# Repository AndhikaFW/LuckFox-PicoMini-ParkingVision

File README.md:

# LuckFox-PicoMini-ParkingVision

A distributed smart parking monitoring vision system utilizing **LuckFox Pico Mini** AI camera boards paired with **ESP32-S3 RAP** nodes, chained together and bridged to a Raspberry Pi 4 backend over wired Ethernet.

Every node in this project is a **parking lot** -- there is no separate entrance/gate node yet (may be added later as its own thing).

---

## System Components (per node)

Each parking-lot node is one **LuckFox Pico Mini** + one **ESP32-S3**, wired together over SPI:

1. **LuckFox Pico Mini (RV1103) -- on-device vision AI**
   - Reads a camera feed, encodes/splits it into **3x 600x400 video streams**.
   - Pipeline per stream: motion detection -> AI car detection -> sleep briefly -> occupancy check (vacant/occupied) -> if occupied, crop + OCR the plate.
   - Sends the 3 encoded video streams and, if present, the cropped plate result to its paired ESP32-S3.

2. **ESP32-S3 RAP (chain relay + one Gateway uplink)**
   - Runs the exact same firmware on every unit (see [`src/ESP32-S3-RAP`](src/ESP32-S3-RAP)); role and chain position come from a small per-unit provisioning step, not a separate build.
   - One designated node (`node_id == 0`, the **Gateway**) also carries a **W5500** module and bridges to the Raspberry Pi 4 backend over a direct Ethernet cable (RJ45) -- it's still a parking-lot node like any other, just the one with this extra uplink role.

---

## Network Architecture: Chain (not a closed ring)

Despite the "RAP" (Ring Access Protocol) name -- kept from this project's original design for naming continuity (`ring_size`, `node_id`, etc. still appear throughout) -- the topology is a **one-way chain**, not a closed loop: there's no "first" node and the Gateway has no outgoing link back into the chain, it only sinks data out to the RPi4.

Every node has its own initiative: it originates its own occupancy/plate reading and video frames on its own schedule, and relays whatever it receives from its upstream neighbor (`prev`) toward its downstream neighbor (`next`) -- both interleaved through the same per-hop link. Two independent transports run in parallel over the same radio:

- **ESP-NOW** -- small `StatusPacket`s (`origin_node_id`, `seq`, `occupied`, `plate`), hop-by-hop with stop-and-wait flow control (a node only accepts a new packet from `prev` once it has room to forward it to `next`).
- **WiFi AP+STA daisy-chain (TCP)** -- bulk video, since raw frames are far too large for ESP-NOW's 250-byte limit. Each frame carries `{origin_node_id, stream_id, seq, data_len}` so its source lot and camera are always identifiable, even after several relay hops.

```mermaid
graph LR
    subgraph "Chain Network (one-way, no closing loop)"
        Node1["Lot 1<br>(LuckFox + ESP32-S3)"] -->|"status/plate + video"| Node2["Lot 2<br>(LuckFox + ESP32-S3)"]
        Node2 -->|"status/plate + video"| Node3["Lot 3<br>(LuckFox + ESP32-S3)"]
        Node3 -->|"status/plate + video"| NodeN["... Lot N-1"]
        NodeN -->|"status/plate + video"| Gateway["Lot 0 / GATEWAY<br>(LuckFox + ESP32-S3 + W5500)"]
    end

    Gateway -->|"RJ45 (W5500), status:5000 video:5300"| RPi["Raspberry Pi 4 backend"]
```

### Why a chain instead of a mesh/star

- **Deterministic, low-collision flow**: every hop is a simple point-to-point link (ESP-NOW unicast + a WiFi AP/STA pair), so there's no contention/arbitration between nodes for a shared medium.
- **Backpressure, not packet loss**: per-hop stop-and-wait means a slow/busy hop naturally throttles the whole chain instead of dropping data silently.
- **Simple cabling-free daisy-chaining**: adding a lot just means provisioning one more node with the next `node_id`; no rewiring of a shared bus or router needed.

Self-healing/re-routing around a permanently dead node is **not** implemented yet -- see `docs/network/topology.md` in the submodule for the full list of current limitations.

---

## Data reaching the backend

Both channels tag every reading/frame with `origin_node_id`, so the Raspberry Pi 4 backend can always tell which lot (and, for video, which of its 3 cameras) a piece of data came from:

| Channel | Port | Content |
| :--- | :--- | :--- |
| Status/plate | 5000 | One line per reading: `node_id:occupied:plate` |
| Video | 5300 | Binary, one frame per message: `{origin_node_id, stream_id, seq, data_len}` + raw frame bytes |

Naming a lot (e.g. "Lot A0") is a Raspberry Pi-side concern, not firmware: see [`backend/node_names.json`](backend/node_names.json) and the demo listener scripts in the same folder (`status_listener.py`, `video_listener.py`), which resolve `node_id -> name` and prove data is separable/displayable per lot. This `backend/` folder is plain Python living directly in this repo (not the ESP32 firmware submodule, and not a submodule itself) -- it's Raspberry Pi-side code, kept separate from the ESP32-S3 firmware.

---

## Getting Started

### Cloning the Repository
```bash
git clone --recurse-submodules https://github.com/AndhikaFW/LuckFox-PicoMini-ParkingVision.git
```

If already cloned without submodules:
```bash
git submodule update --init --recursive
```

### Layout

- [`src/ESP32-S3-RAP`](src/ESP32-S3-RAP) -- ESP32-S3 firmware **only** (its own git submodule/repo). Build/flash/provisioning instructions and the full protocol/topology write-up live there: [`docs/network/topology.md`](src/ESP32-S3-RAP/docs/network/topology.md).
- [`backend/`](backend) -- Raspberry Pi 4-side Python (demo listeners + `node_names.json`). Plain files in this repo, not inside the firmware submodule and not a submodule of its own -- there's nothing here that needs its own version history separate from the rest of this repo.

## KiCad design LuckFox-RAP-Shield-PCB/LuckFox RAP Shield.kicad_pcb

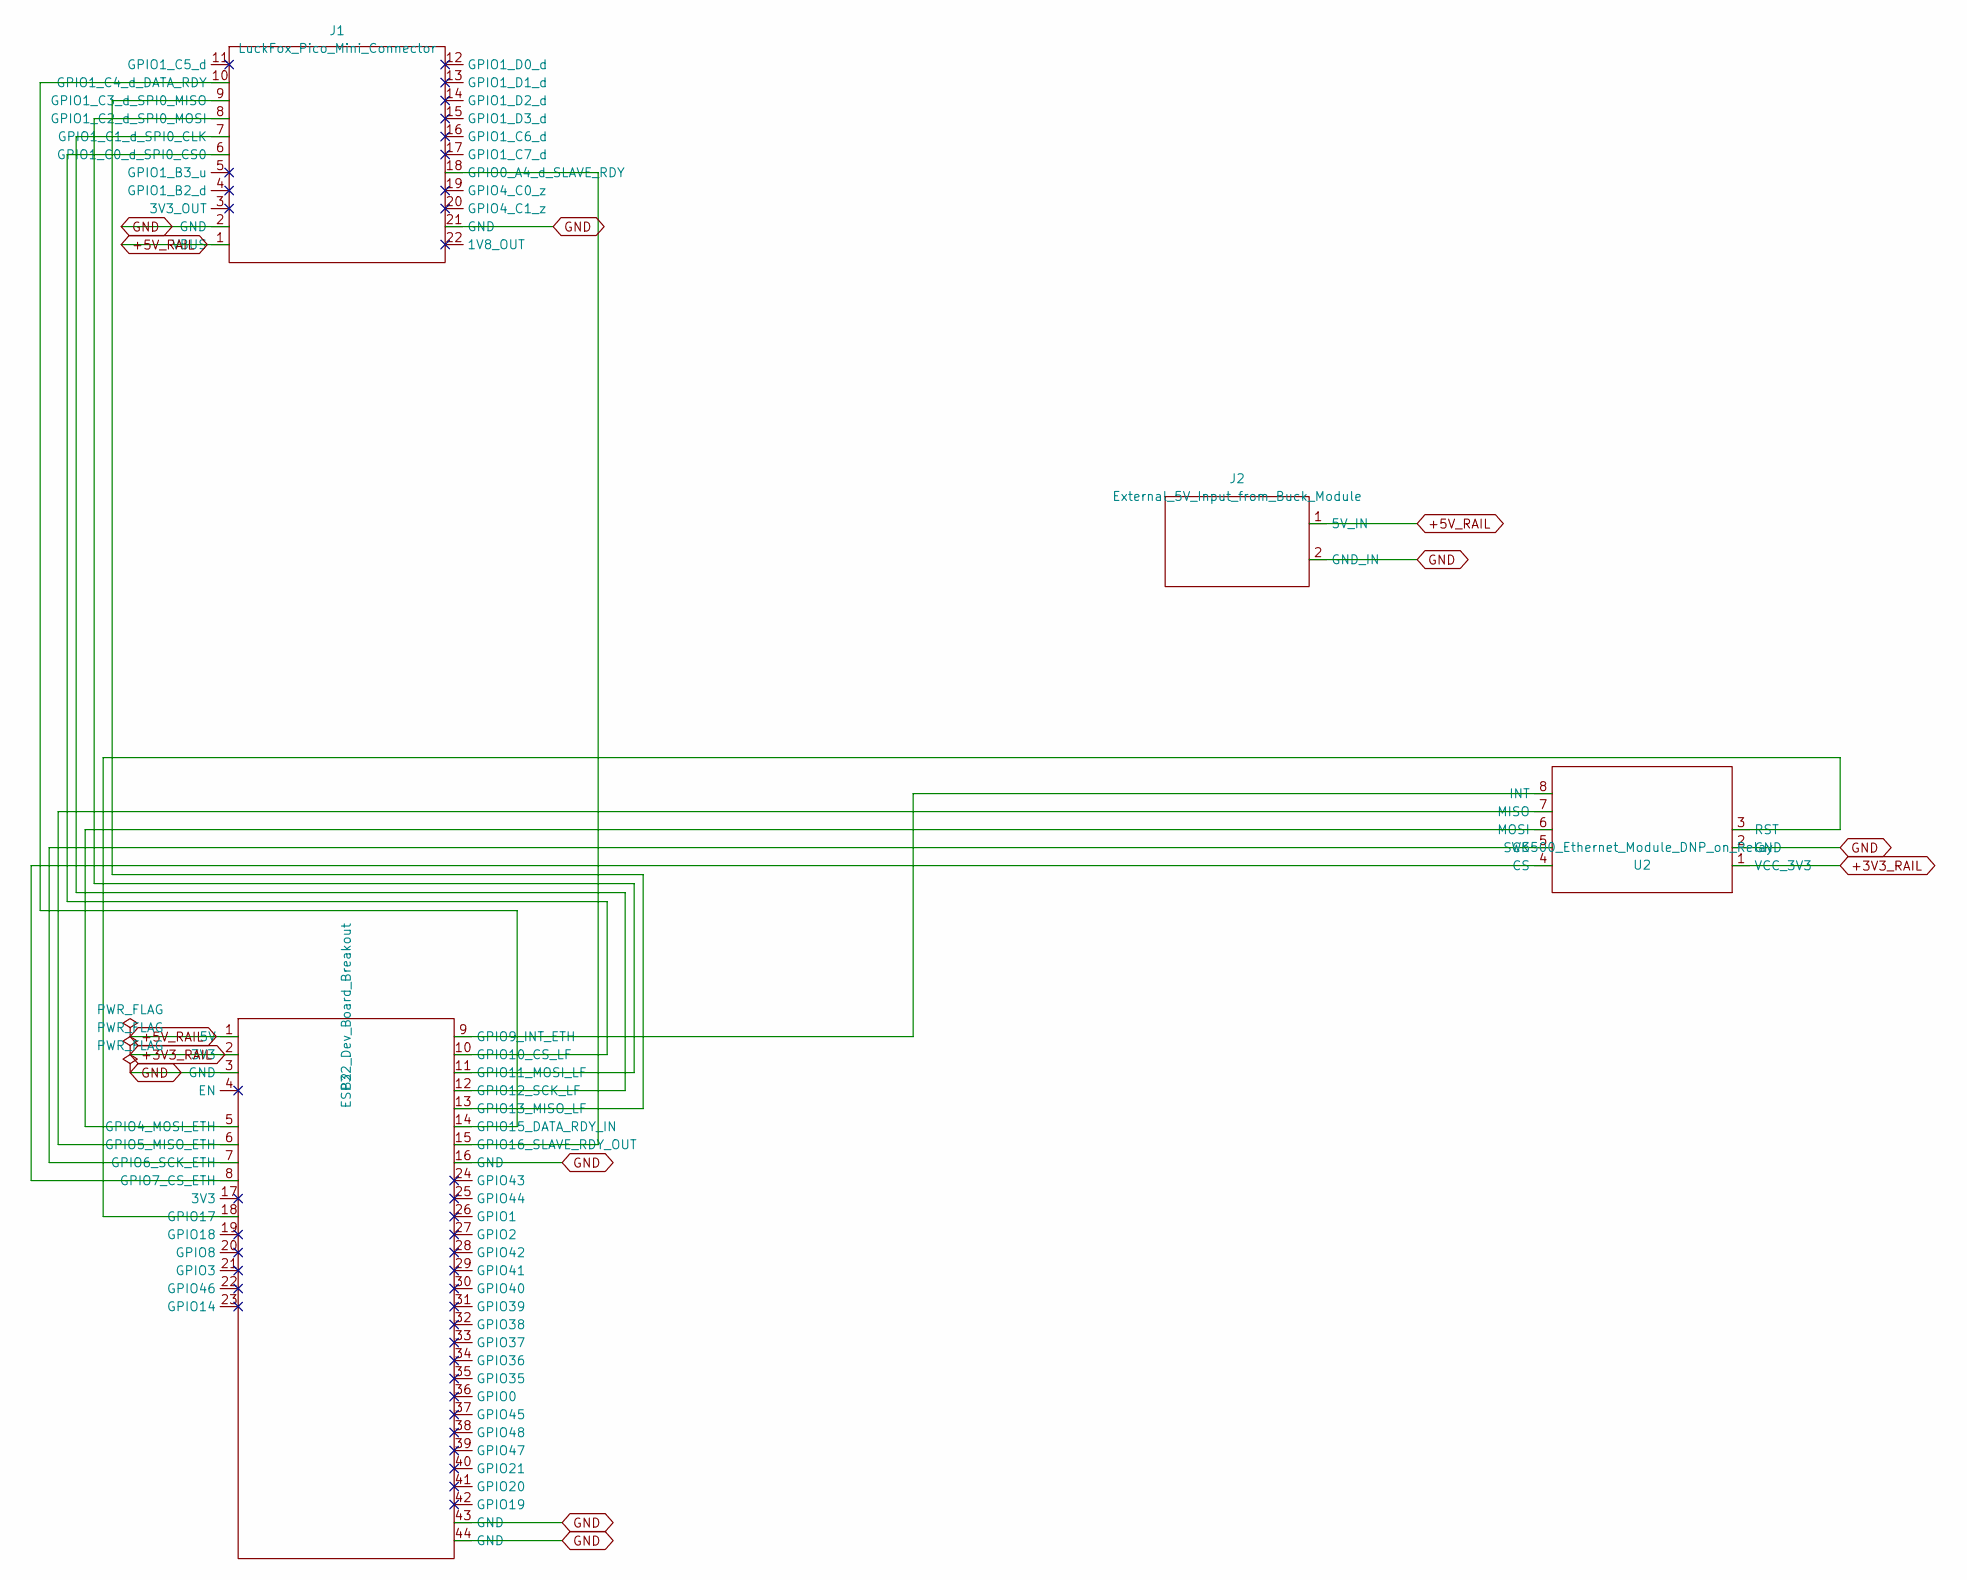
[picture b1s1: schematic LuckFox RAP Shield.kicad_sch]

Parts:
B2: ESP32_Dev_Board_Breakout
J1: LuckFox_Pico_Mini_Connector; LuckFox_Pico_Mini
J2: External_5V_Input_from_Buck_Module; PinHeader_1x02_P2.54mm_Vertical
U2: W5500_Ethernet_Module_DNP_on_Relay; PinHeader_1x08_P2.54mm_Vertical

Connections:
+3V3_RAIL: B2.2 (3V3), U2.1 (VCC_3V3)
+5V_RAIL: B2.1 (5V), J1.1 (VBUS), J2.1 (5V_IN)
GND: B2.3 (GND), B2.16 (GND), B2.43 (GND), B2.44 (GND), J1.2 (GND), J1.21 (GND), J2.2 (GND_IN), U2.2 (GND)
unnamed: B2.5 (GPIO4_MOSI_ETH), U2.6 (MOSI)
unnamed: B2.6 (GPIO5_MISO_ETH), U2.7 (MISO)
unnamed: B2.7 (GPIO6_SCK_ETH), U2.5 (SCK)
unnamed: B2.8 (GPIO7_CS_ETH), U2.4 (CS)
unnamed: B2.9 (GPIO9_INT_ETH), U2.8 (INT)
unnamed: B2.10 (GPIO10_CS_LF), J1.6 (GPIO1_C0_d_SPI0_CS0)
unnamed: B2.11 (GPIO11_MOSI_LF), J1.8 (GPIO1_C2_d_SPI0_MOSI)
unnamed: B2.12 (GPIO12_SCK_LF), J1.7 (GPIO1_C1_d_SPI0_CLK)
unnamed: B2.13 (GPIO13_MISO_LF), J1.9 (GPIO1_C3_d_SPI0_MISO)
unnamed: B2.14 (GPIO15_DATA_RDY_IN), J1.10 (GPIO1_C4_d_DATA_RDY)
unnamed: B2.15 (GPIO16_SLAVE_RDY_OUT), J1.18 (GPIO0_A4_d_SLAVE_RDY)
unnamed: B2.18 (GPIO17), U2.3 (RST)

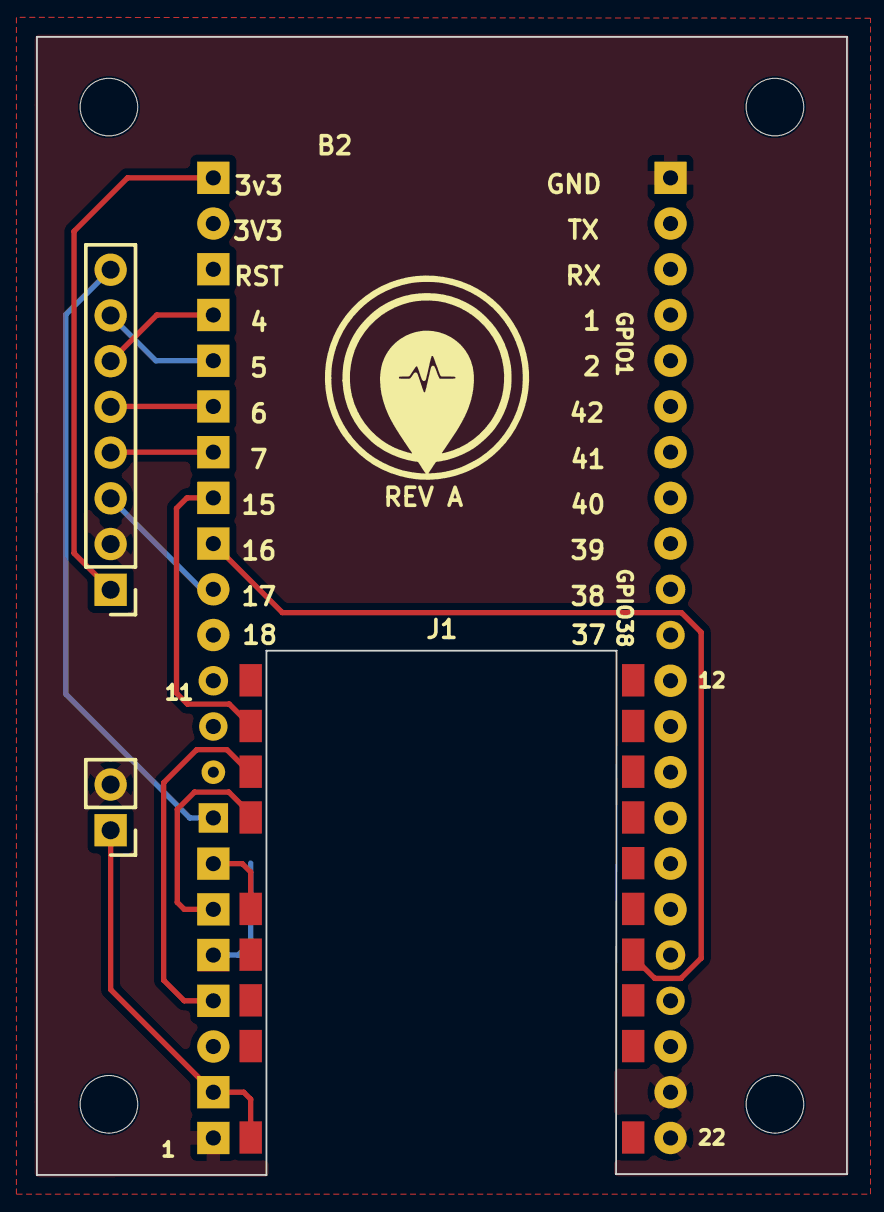
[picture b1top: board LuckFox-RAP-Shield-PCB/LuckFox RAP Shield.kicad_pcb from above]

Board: 2 copper layers, 45.0 x 63.2 mm, 8 parts (1 on the bottom side), 15 nets.

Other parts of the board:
H1, H2, H3, H4: MountingHole_3.2mm_M3

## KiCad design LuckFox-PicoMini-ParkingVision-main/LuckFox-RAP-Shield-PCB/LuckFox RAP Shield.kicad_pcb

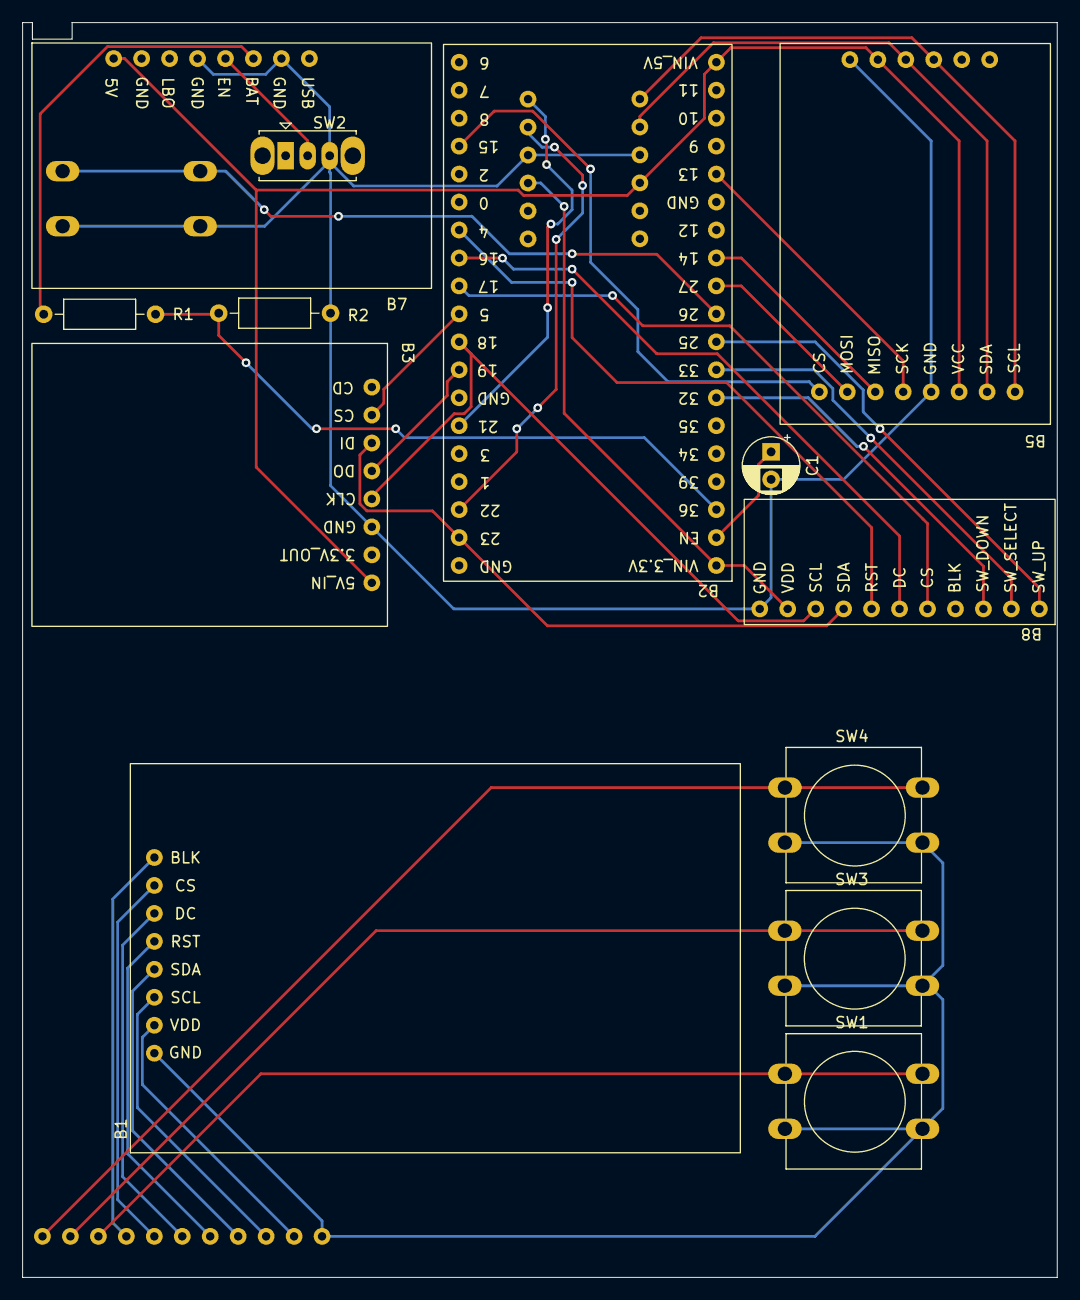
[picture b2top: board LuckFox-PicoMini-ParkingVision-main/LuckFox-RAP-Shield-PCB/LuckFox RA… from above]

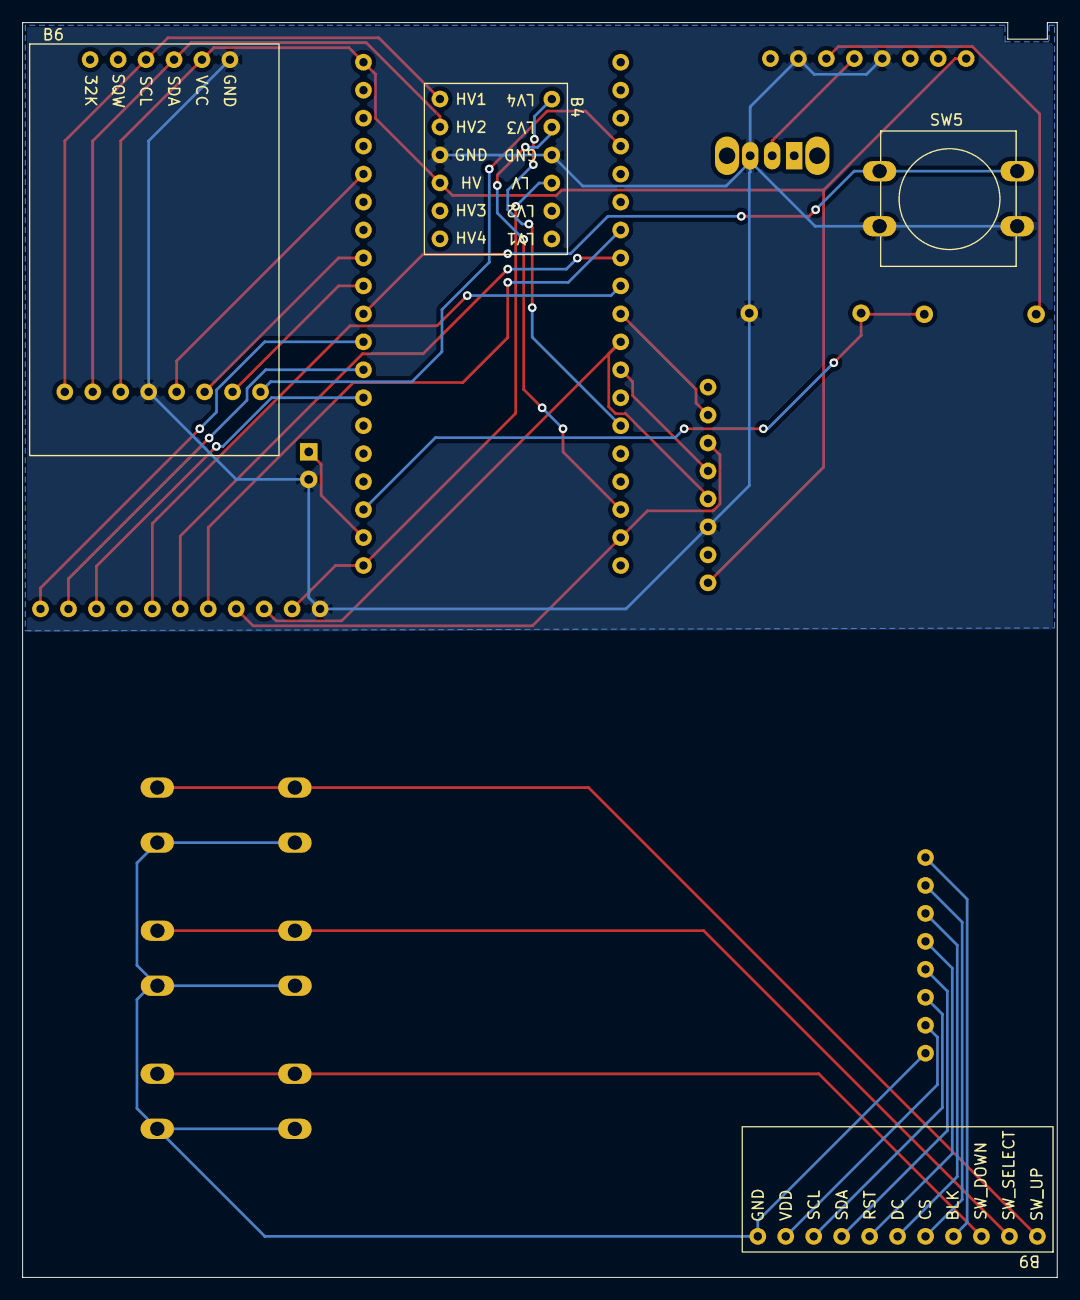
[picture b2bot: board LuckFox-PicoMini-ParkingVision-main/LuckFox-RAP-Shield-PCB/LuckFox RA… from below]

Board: 2 copper layers, 94.0 x 114.0 mm, 17 parts (4 on the bottom side), 37 nets.

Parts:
B1: ST7735_160x128_TFT_Breakout
B2: ESP32_Dev_Board_Breakout
B3: Adafruit_MicroSD_Card_Breakout
B4: I2C_Level_Shifter_Breakout
B5: ArduCam_OV2640_Breakout
B6: RTC_Breakout
B7: PowerBoost_500_Breakout; Adafruit_PowerBoost_500_Breakout
B8, B9: ESP32_Camera_Multi_PCB_pins
C1: 10uF; CP_Radial_D5.0mm_P2.50mm
R1, R2: 100K; R_Axial_DIN0207_L6.3mm_D2.5mm_P10.16mm_Horizontal
SW1: SW_DOWN; SW_PUSH-12mm
SW2: SW_SPDT; SW_Slide_1P2T_CK_OS102011MS2Q
SW3: SW_SELECT; SW_PUSH-12mm
SW4: SW_UP; SW_PUSH-12mm
SW5: SW_SHUTTER; SW_PUSH-12mm

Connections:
+3V3: B2.1 (VIN_3.3V), B4.4 (LV), B8.10 (VDD)
+5V: B2.19 (VIN_5V), B3.8 (5V_IN), B4.9 (HV), B5.6 (VCC), B6.5 (VDD), B7.1 (5V)
GND: B3.6 (GND), B4.3 (GND), B4.10 (GND), B5.5 (GND), B6.6 (GND), B7.4 (GND), B7.7 (GND), B8.11 (GND), C1.2, R2.1, SW2.3 (C), SW5.2
unnamed: B1.1 (GND), B9.11 (GND), SW1.2, SW3.2, SW4.2
unnamed: B1.2 (VDD), B9.10 (VDD)
unnamed: B1.3 (SCL), B9.9 (SCL)
unnamed: B1.4 (SDA), B9.8 (SDA)
unnamed: B1.5 (RST), B9.7 (RST)
unnamed: B1.6 (DC), B9.6 (DC)
unnamed: B1.7 (CS), B9.5 (CS)
unnamed: B1.8 (BLK), B9.4 (BLK)
unnamed: B2.2 (EN), C1.1
unnamed: B2.3 (36), R1.1, R2.2
unnamed: B2.7 (32), B8.3 (SW_DOWN)
unnamed: B2.8 (33), B8.2 (SW_SELECT)
unnamed: B2.9 (25), B8.1 (SW_UP)
unnamed: B2.10 (26), SW5.1
unnamed: B2.11 (27), B5.2 (MOSI)
unnamed: B2.12 (14), B5.3 (MISO)
unnamed: B2.15 (13), B5.4 (SCK)
unnamed: B2.21 (23), B3.3 (DI), B8.8 (SDA)
unnamed: B2.22, B4.2 (LV3)
unnamed: B2.25 (21), B4.1 (LV4)
unnamed: B2.27 (19), B3.4 (DO)
unnamed: B2.28 (18), B3.5 (CLK), B8.9 (SCL)
unnamed: B2.29 (5), B3.2 (CS)
unnamed: B2.30 (17), B8.5 (CS)
unnamed: B2.31 (16), B8.6 (DC)
unnamed: B2.32 (4), B8.7 (RST)
unnamed: B2.35 (15), B5.1 (CS)
unnamed: B4.11 (HV2), B5.7 (SDA), B6.4 (SDA)
unnamed: B4.12 (HV1), B5.8 (SCL), B6.3 (SCL)
unnamed: B7.5 (EN), SW2.2 (B)
unnamed: B7.6 (BAT), R1.2
unnamed: B9.1 (SW_UP), SW4.1
unnamed: B9.2 (SW_SELECT), SW3.1
unnamed: B9.3 (SW_DOWN), SW1.1
